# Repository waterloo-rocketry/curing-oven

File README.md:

# curing-oven

repository to store all the code and data for the curing oven project

call/text Calvin DeKoter at 650-399-6428 to ask about the project / or give UI tips

TODO 

Things to Fix

	Firmware

		List of issues detailed in powerpoint and also in the code itself
		General performance / best practice things could also be better

	Electrical
		
		There are some layout issues - currently the pressure sensor has been flywired
		A few other flywires and cut traces on the indicator LEDs

		Analog inputs and outputs are untested

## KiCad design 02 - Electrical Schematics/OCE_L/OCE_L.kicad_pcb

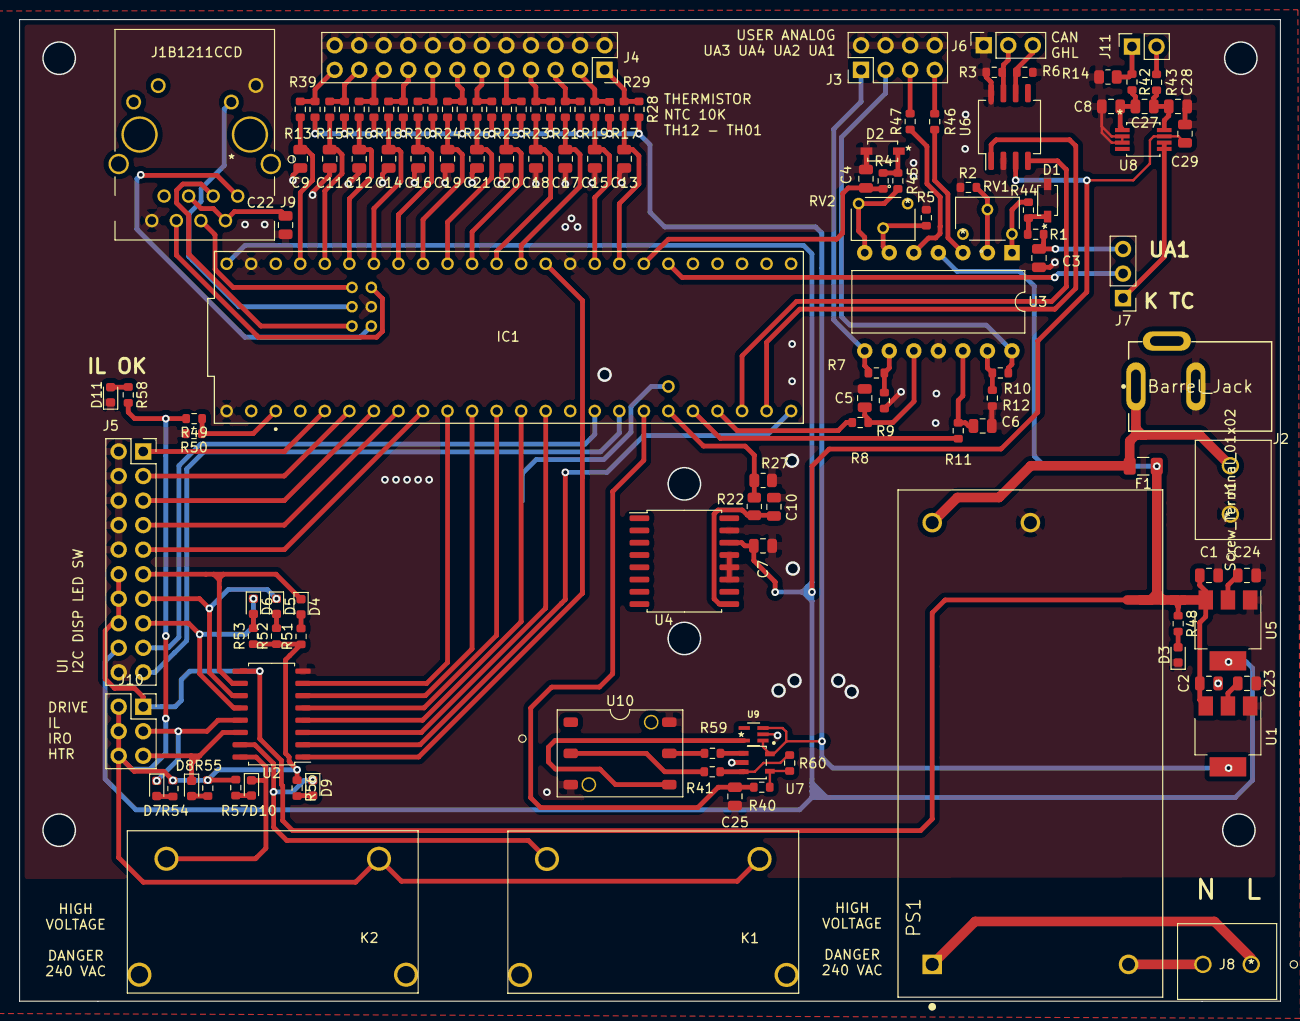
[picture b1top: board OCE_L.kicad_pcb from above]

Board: 2 copper layers, 130.5 x 101.6 mm, 128 parts (1 on the bottom side), 109 nets.

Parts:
B1: BK-912-TR
C1, C2: 10 uF; C_0805_2012Metric
C3, C4, C5, C6, C16, C22: 0.1uF; C_0805_2012Metric
C7, C10: 47 nF; C_0805_2012Metric
C8, C25, C28: 1 uF; C_0805_2012Metric
C9, C11, C12, C13, C14, C15, C17, C18, C19, C20, C21: 10uF; C_0805_2012Metric
C23, C24: 22 uF; C_0805_2012Metric
C27: 1 nF; C_0805_2012Metric
C29: 0.1 uF; C_0805_2012Metric
D1, D2: Zener_3.3; MMSZ3V3T1G
D3, D4, D5, D6, D7, D8, D9, D10, D11: LED; LED_0603_1608Metric
F1: 1 A 1206 Fuse; Fuse_1206_3216Metric
IC1: DEV-16771; MODULE_DEV-16771
J1, J8: Screw_Terminal_01x02; oce
J2: Barrel_Jack; Kycon-KLDX-0202-A-MFG
J3: Conn_02x04_Counter_Clockwise; PinHeader_2x04_P2.54mm_Vertical_Lin
J4: Conn_01x24_Female; PinSocket_2x12_P2.54mm_Vertical
J5: Conn_02x10_Odd_Even; PinSocket_2x10_P2.54mm_Vertical
J6: Conn_01x03_Female; PinSocket_1x03_P2.54mm_Vertical
J7: Conn_01x03_Male; PinHeader_1x03_P2.54mm_Vertical
J9: J1B1211CCD
J10: Conn_02x03_Odd_Even; PinSocket_2x03_P2.54mm_Vertical
J11: Conn_01x02_Female; PinSocket_1x02_P2.54mm_Vertical
K1, K2: J120D
PS1: RAC10-12SK_277; CONV_RAC10-12SK_277
R1, R2, R4, R5, R8, R9, R11, R12, R13, R15, R16, R17, R18, R19, R20, R21, R23, R24, R25, R26, R40, R42, R43, R46, R47, R49: 10k; R_0603_1608Metric
R3, R6: 60; R_0603_1608Metric
R7, R10: 40k; R_0603_1608Metric
R14: 1M; R_0805_2012Metric
R22: 3.3k; R_0805_2012Metric
R27: 4.7k; R_0805_2012Metric
R28, R29, R30, R31, R32, R33, R34, R35, R36, R37, R38, R39, R41, R44, R45, R48, R51, R52, R53, R54, R55, R56, R57, R58, R59: 1k; R_0603_1608Metric
R50: 2.5k; R_0603_1608Metric
R60: 100k; R_0603_1608Metric
RV1, RV2: R_POT; 64WR50KLF
U1: AZ1117-3.3; SOT-223-3_TabPin2
U2: ULQ2004A; SOIC-16_4.55x10.3mm_P1.27mm
U3: LM324; DIP-14_W10.16mm
U4: MLX90809
U5: AZ1117-5.0; SOT-223-3_TabPin2
U6: TJA1044
U7: AS321KTR-G1
U8: AD8494ARMZ
U9: MIC5366-1.8YC5-TR; SOT65P210X110-5N
U10: BLC-L01D-U2

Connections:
1V8: U9.5, U10.3
3V3: C23.1, R28.2, R29.2, R30.2, R31.2, R32.2, R33.2, R34.2, R35.2, R36.2, R37.2, R38.2, R39.2, U1.2, U7.5, U9.1, U9.3
5V: C7.1, C24.2, C29.1, J5.18, U4.3, U5.2, U6.3, U8.7
12V: F1.2, J1.2, J2.1, PS1.5
12V_F: C1.1, C2.2, F1.1, J5.12, J5.14, J5.16, J10.1, R48.1, U1.3, U2.9, U3.4, U5.3
12V_IL: J10.2, J10.4, J10.6, K1.1, K2.1, R49.2, R51.1, R52.1, R53.1, R54.1, R55.1, R56.1, R57.1, R58.2
AUX1: D9.1, K1.2, U2.15
AUX1_EN: IC1.32, U2.2
BLC_VOUTM: R41.1, R60.1, U7.3
BLC_VOUTP: R59.2, U7.1
BLW1: D10.1, K2.2, U2.16
BLW1_EN: IC1.13, U2.1
CAN_RX: IC1.30, U6.4
CAN_TX: IC1.31, U6.1
ETH_LED: IC1.LED, J9.10
ETH_RX+: IC1.R+, J9.4
ETH_RX-: IC1.R-, J9.6
ETH_TX+: IC1.T+, J9.1
ETH_TX-: IC1.T-, J9.3
GND: B1.3, C1.2, C2.1, C3.2, C4.2, C5.2, C6.2, C7.2, C8.1, C9.2, C10.2, C11.2, C12.2, C13.2, C14.2, C15.2, C16.2, C17.2, C18.2, C19.2, C20.2, C21.2, C22.1, C23.2, C24.1, C25.1, C28.1, C29.2, D1.2, D2.2, D3.1, D11.1, IC1.GND1, IC1.GND2, IC1.GND3, IC1.GND5, J1.1, J2.2, J3.5, J3.6, J3.7, J3.8, J4.2, J4.4, J4.6, J4.8, J4.10, J4.12, J4.14, J4.16, J4.18, J4.20, J4.22, J4.24, J5.2, J5.4, J5.6, J5.8, J5.10, J5.20, J6.1, J9.8, J9.9, PS1.4, R2.2, R3.2, R5.2, R6.2, R9.1, R12.1, R14.2, R27.1, R50.2, U1.1, U2.8, U3.11, U4.2, U4.4, U4.5, U4.6, U5.1, U6.2, U6.8, U7.2, U8.2, U8.3, U9.2, U10.1, U10.6
HTR1: D8.1, J10.5, U2.14
HTR1_EN: IC1.12, U2.3
IRO1: D7.1, J10.3, U2.13
IRO1_EN: IC1.11, U2.4
LED1: IC1.8, U2.7
LED1_DR: D4.1, J5.11, U2.10
LED2: IC1.9, U2.6
LED2_DR: D5.1, J5.13, U2.11
LED3: IC1.10, U2.5
LED3_DR: D6.1, J5.15, U2.12
unnamed: C3.1, J7.3, R1.2
unnamed: C5.1, R8.1, U3.10
unnamed: C6.1, R11.1, U3.12
unnamed: C10.1, R22.2, U4.8
unnamed: C22.2, J9.2, J9.5
unnamed: C27.1, C28.2, R43.1, U8.8
unnamed: C8.2, C27.2, R42.1, U8.1
unnamed: D1.1, R1.1, R44.2
unnamed: D2.1, R4.1, R45.2
unnamed: D3.2, R48.2
unnamed: D4.2, R51.2
unnamed: D5.2, R52.2
unnamed: D6.2, R53.2
unnamed: D7.2, R54.2
unnamed: D8.2, R55.2
unnamed: D9.2, R56.2
unnamed: D10.2, R57.2
unnamed: D11.2, R58.1
unnamed: J3.1, R7.2, U3.8
unnamed: J3.2, R10.2, U3.14
unnamed: J3.3, R47.2
unnamed: J3.4, R46.2
unnamed: J4.1, R17.1, R28.1
unnamed: J4.3, R19.1, R29.1
unnamed: J4.5, R21.1, R30.1
unnamed: J4.7, R23.1, R31.1
unnamed: J4.9, R25.1, R32.1
unnamed: J4.11, R26.1, R33.1
unnamed: J4.13, R24.1, R34.1
unnamed: J4.15, R20.1, R35.1
unnamed: J4.17, R18.1, R36.1
unnamed: J4.19, R16.1, R37.1
unnamed: J4.21, R15.1, R38.1
unnamed: J4.23, R13.1, R39.1
unnamed: J6.2, R3.1, U6.7
unnamed: J6.3, R6.1, U6.6
unnamed: J7.1, U8.5, U8.6
unnamed: J8.1, PS1.1
unnamed: J8.2, PS1.2
unnamed: J11.1, R14.1, R42.2
unnamed: J11.2, R43.2
unnamed: R2.1, RV1.2, U3.2
unnamed: R5.1, RV2.2, U3.6
unnamed: R7.1, R9.2, U3.9
unnamed: R10.1, R12.2, U3.13
unnamed: R40.1, R60.2, U7.4
unnamed: R41.2, U10.5
unnamed: R44.1, RV1.3, U3.1
unnamed: R45.1, RV2.3, U3.7
unnamed: R46.1, U3.3
unnamed: R47.1, U3.5
unnamed: R59.1, U10.2
PIT1: C25.2, IC1.26, R40.2
SCL2: IC1.24, J5.17
SDA2: IC1.25, J5.19
SEN_IL: IC1.1, R49.1, R50.1
SW1: IC1.3, J5.1
SW2: IC1.4, J5.3
SW3: IC1.5, J5.5
SW4: IC1.6, J5.7
SW5: IC1.7, J5.9
TH01_IN: C13.1, IC1.40, R17.2
TH02_IN: C15.1, IC1.41, R19.2
TH03_IN: C17.1, IC1.14, R21.2
TH04_IN: C18.1, IC1.15, R23.2
TH05_IN: C20.1, IC1.16, R25.2
TH06_IN: C21.1, IC1.17, R26.2
TH07_IN: C19.1, IC1.18, R24.2
TH08_IN: C16.1, IC1.19, R20.2
TH09_IN: C14.1, IC1.20, R18.2
TH10_IN: C12.1, IC1.21, R16.2
TH11_IN: C11.1, IC1.22, R15.2
TH12_IN: C9.1, IC1.23, R13.2
UA1: IC1.38, J7.2
UA2: C4.1, IC1.39, R4.2
UA3_OUT: IC1.29, R8.2
UA4_OUT: IC1.28, R11.2
VBAT: B1.1, B1.2, IC1.VBAT
VS1: IC1.27, R22.1, R27.2

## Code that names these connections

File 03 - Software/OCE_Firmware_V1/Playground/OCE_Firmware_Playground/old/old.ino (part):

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bool AIN_u[] = {true,true,true,true,true,true,true,true,true,false,false,false,false,false,false,false} ; // Array to select whether or not to collect data from the analog input
bool AIN_avg[] = {true,true,true,false,false,false,true,true,true,false,false,false,false,false,false,false}; // Array to select whether or not to include the thermistors in the oven temperarature average - note that the last 4 are always false, as they are not temperatures
// If the pin is in use, mark it to be read during the cure and cool states
const char *AIN_n[] = {"TH01","TH02","TH03","TH04","TH05","TH06","TH07","TH08","TH09","TH10","TH11","TH12","UA1","UA2","VS1","PIT1"} ;
// Names of all the analog input pins

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
int DRV_c = 7 ;
int DRV[] = {11,13,12,32,8,9,10}; // Input Relay, Blower, Heater, Auxiliary, and LED Enable Pins 
const char *DRV_n[] = {"IRO1","BLW1","HTR1","AUX1","LED1","LED2","LED3"};

int state = 1 ; // Start in the startup state
const char *state_n[] = {"OFF","STARTUP","CURE","COOL","ERROR"} ;

int SEN_IL = 1 ;
int UA3 = 29 ;
int UA4 = 28 ;

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
volatile int cycle = 1 ;
volatile int control_HTR1_count = 0 ;
volatile int control_HTR1 = 0 ; // Range of time HTR1 is enabled, over 1 second - 0 - 59 out of 60 electrical cycles

// Data Structures
const int data_width = 1 + 1 + AIN_c + 1 ; // Time plus Temp_set plus analog plus control setpoint
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    pinMode(DRV[k],OUTPUT) ;
  }

  pinMode(SEN_IL,INPUT_PULLDOWN) ;
  attachInterrupt(digitalPinToInterrupt(SEN_IL), ILBRK, FALLING) ;
  
  pinMode(UA3,OUTPUT) ;
  pinMode(UA4,OUTPUT) ;
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void pushRUN()
{RUN = true;}

void ILBRK() // Using an interrupt, watch for the SEN_IL pin falling from high to low
{
  ILOK = false ; // Indicate the IL state as broken
  state = 4 ;
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
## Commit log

2023-02-23 Upload mechanical CAD
2023-02-23 Firmware Upload
2023-02-23 Added electrical schematics
2023-02-23 Updated readme with TODO
2023-03-03 Added I2C Wire2 library
2023-03-04 Updated the panel schematic, added new files
2023-03-04 third try
2023-03-04 Removing unecessary files
2023-03-04 removed otherfiles
2023-03-04 deleted file
2023-03-04 Updated CuringOvenWiring with wire labels
2023-03-05 Updated electrical schematic with Shirleys feedback
2023-03-06 More tweaks to diagram
2023-03-25 Updated wiring schematic with inspectors feedback
2023-05-16 Working on digital twin
2023-05-16 Moved schematics to google drive

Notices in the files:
parts and their libraries:
Copyright 2021 Accelerated Designs. All rights reserved.
